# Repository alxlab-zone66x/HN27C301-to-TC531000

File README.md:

# HN27C301 to TC53100

This is a DIP non-JEDEC 1M (128Kx8) EPROM to TC531000 MROM adapter. This can be used in various systems like a Macintosh SE or Apple IIGS that uses the TC531000 for it's ROM. 

Here's a list of non-JEDEC 1M (128Kx8) EPROMs that will work with this adapter:

- AMD 27C100
- Fujitsu MBM27C1000
- Hitachi HN27C301
- Intel 27C100
- Macronix MX27C1001
- NEC D27C1000
- Sony CXK27C100
- ST M27C1000
- ST ST27C1000
- Toshiba TC571001

## Instructions

After programming your EPROM, solder this adapter to the underside of the chip and bridge the four solder jumpers. 

If you need to reprogram the EPROM you need to desolder the jumpers.

The jumper side of the PCB should overhang the socket.

## Manufacturing

The release includes the manufacturing files for JLCPCB specifically. If you need to the gerber files, BOM or component pick & place in a different format then you would have to generate them yourself.

The PCB thickness chosen should be as thin as possible. I've used 0.8mm PCBs and it was ok on a Mac SE socket.

## License

HN27C301 to TC53100 by [Alexandre Marcoux](https://github.com/alxlab-zone66x/Apple-SWIM-Chip-Adapters) licensed under a <a rel="license" href="http://creativecommons.org/licenses/by-nc-sa/4.0/">Creative Commons Attribution-NonCommercial-ShareAlike 4.0 International License</a>.

## Community

For more great retro hardware projects and a great community check out:

Join us in #TinkerDiffernt on [Discord](https://discord.gg/GrKnnNmt) to help make retro solutions available to all.

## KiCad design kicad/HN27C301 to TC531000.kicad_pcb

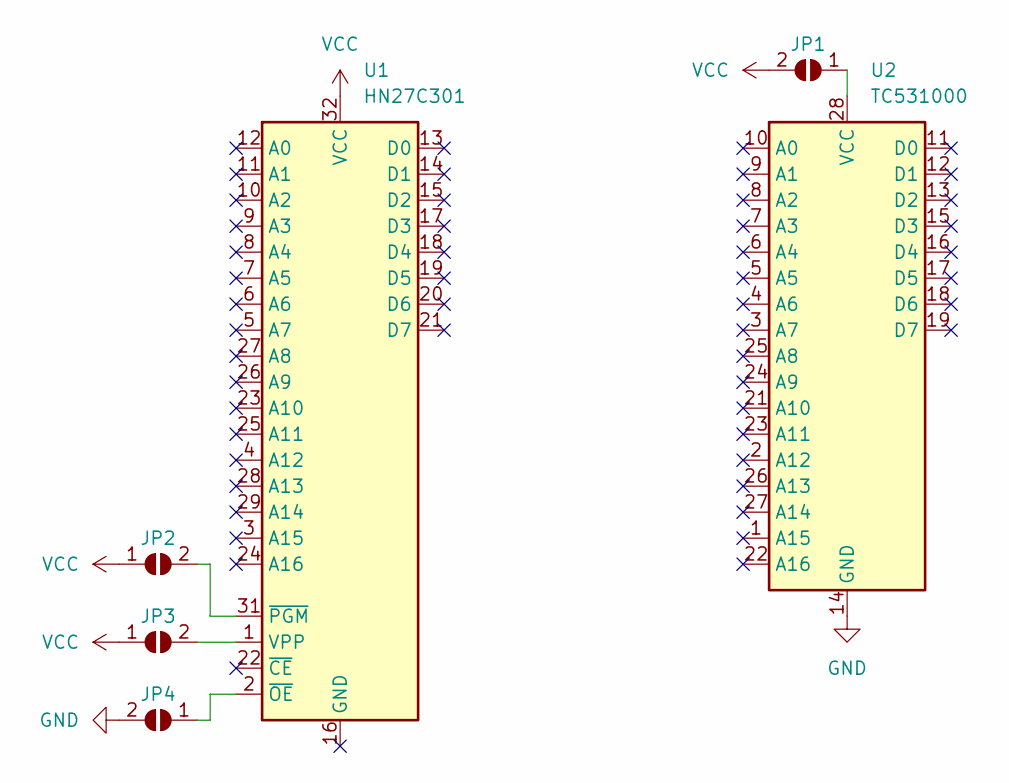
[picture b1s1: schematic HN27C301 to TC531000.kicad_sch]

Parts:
JP1, JP2, JP3, JP4: SolderJumper_2_Open; SolderJumper-2_P1.127mm_Open_RoundedPad1.0x1.2mm
U1: HN27C301; HN27C301-to-TC531000_DIP-32_W15.24mm_LongPads
U2: TC531000; HN27C301-to-TC531000_DIP-28_W15.24mm_LongPads

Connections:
GND: JP4.2 (B), U2.14 (GND)
unnamed: JP1.1 (A), U2.28 (VCC)
unnamed: JP2.2 (B), U1.31 (~PGM)
unnamed: JP3.2 (B), U1.1 (VPP)
unnamed: JP4.1 (A), U1.2 (~OE)
VCC: JP1.2 (B), JP2.1 (A), JP3.1 (A), U1.32 (VCC)

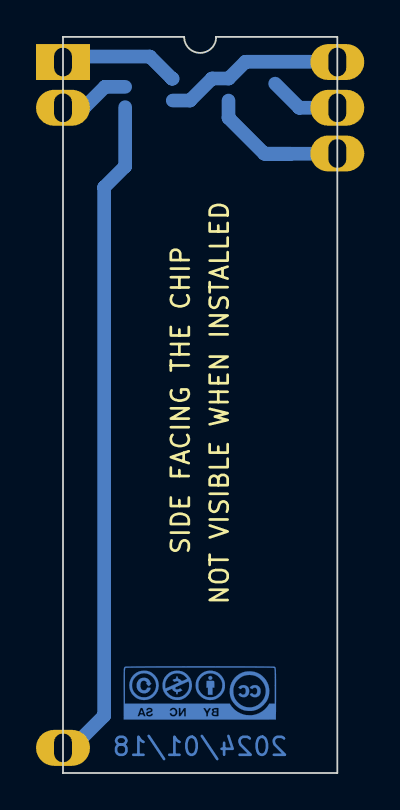
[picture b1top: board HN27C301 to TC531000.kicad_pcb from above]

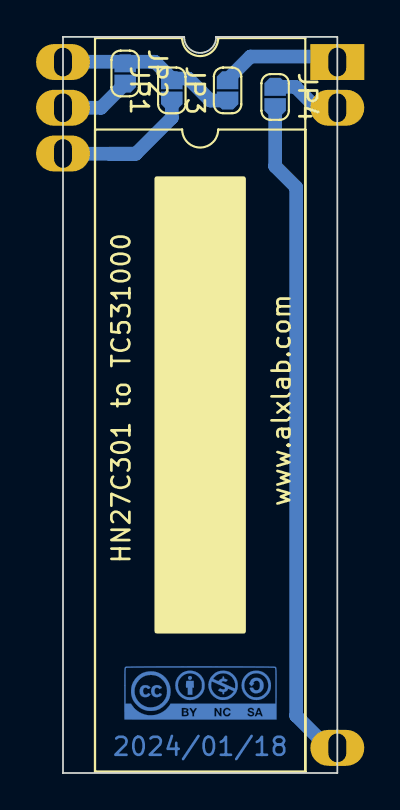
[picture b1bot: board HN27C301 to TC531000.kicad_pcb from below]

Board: 2 copper layers, 15.2 x 40.9 mm, 6 parts (4 on the bottom side), 6 nets.
